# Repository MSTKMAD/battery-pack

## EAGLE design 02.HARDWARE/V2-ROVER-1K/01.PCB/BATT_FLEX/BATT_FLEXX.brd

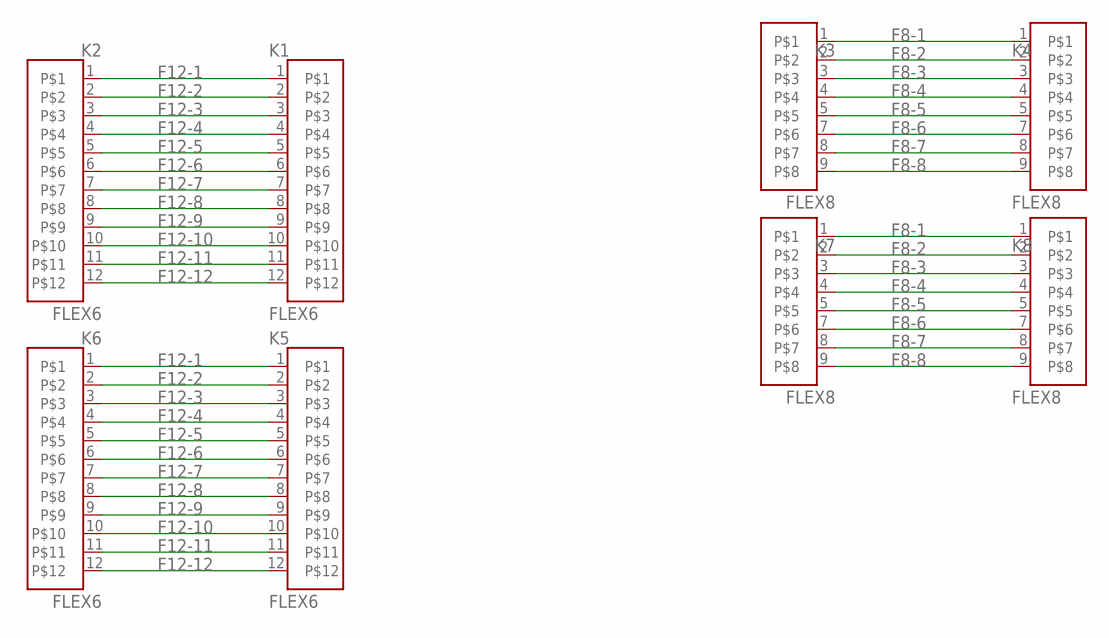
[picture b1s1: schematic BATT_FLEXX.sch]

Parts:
K1, K2, K5, K6: FLEX6
K3, K4, K7, K8: FLEX8

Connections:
F8-1: K3.1, K4.1, K7.1, K8.1
F8-2: K3.2, K4.2, K7.2, K8.2
F8-3: K3.3, K4.3, K7.3, K8.3
F8-4: K3.4, K4.4, K7.4, K8.4
F8-5: K3.5, K4.5, K7.5, K8.5
F8-6: K3.7, K4.7, K7.7, K8.7
F8-7: K3.8, K4.8, K7.8, K8.8
F8-8: K3.9, K4.9, K7.9, K8.9
F12-1: K1.1, K2.1, K5.1, K6.1
F12-2: K1.2, K2.2, K5.2, K6.2
F12-3: K1.3, K2.3, K5.3, K6.3
F12-4: K1.4, K2.4, K5.4, K6.4
F12-5: K1.5, K2.5, K5.5, K6.5
F12-6: K1.6, K2.6, K5.6, K6.6
F12-7: K1.7, K2.7, K5.7, K6.7
F12-8: K1.8, K2.8, K5.8, K6.8
F12-9: K1.9, K2.9, K5.9, K6.9
F12-10: K1.10, K2.10, K5.10, K6.10
F12-11: K1.11, K2.11, K5.11, K6.11
F12-12: K1.12, K2.12, K5.12, K6.12

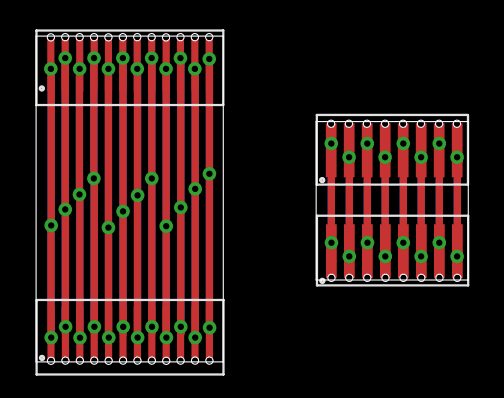
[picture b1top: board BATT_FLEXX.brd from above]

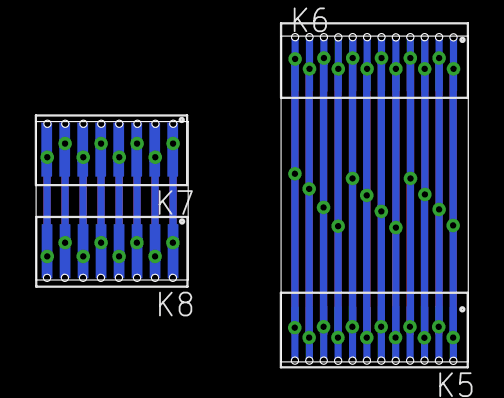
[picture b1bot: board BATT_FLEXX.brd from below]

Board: 2 copper layers, 24.0 x 18.1 mm, 8 parts (4 on the bottom side), 20 nets.

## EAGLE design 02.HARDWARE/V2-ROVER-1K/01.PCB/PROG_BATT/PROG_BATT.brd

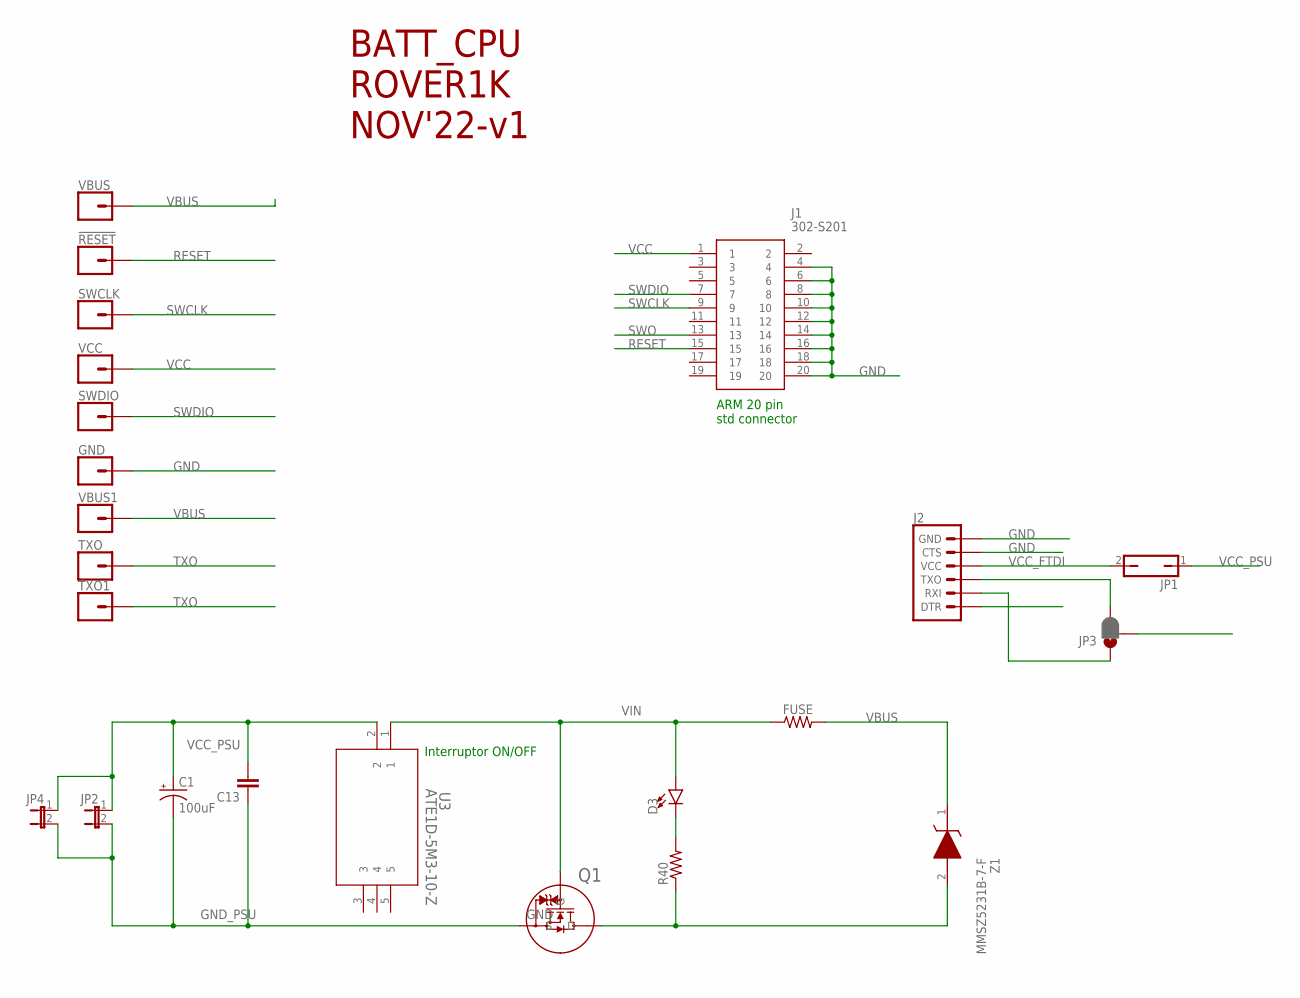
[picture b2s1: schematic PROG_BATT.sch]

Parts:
!RESET: CONN_01POGOPIN_HOLE_LARGE; 1X01_POGOPIN_HOLE_0.061_DIA
C1: 100uF; CPOL-RADIAL-2.5MM-6.5MM
C13: C-EUC0805; C0805
D3: LED3MM; LED_3MM
FUSE: 0805
GND: CONN_01POGOPIN_HOLE_LARGE; 1X01_POGOPIN_HOLE_0.061_DIA
J1: 302-S201; SHDR20W66P254_2X10_3300X905X90
J2: 6_PIN_SERIAL_TARGET; 1X06
JP1: JP1Q; JP1
JP2, JP4: JP1E; JP1
JP3: JUMPER-SMT_3_1-NC_PASTE_NO-SILK; SMT-JUMPER_3_1-NC_PASTE_NO-SILK
Q1: PJA3416AE_R1_00001; SOT23_PJA3416_PNJ
R40: 10K; 0805
SWCLK: CONN_01POGOPIN_HOLE_LARGE; 1X01_POGOPIN_HOLE_0.061_DIA
SWDIO: CONN_01POGOPIN_HOLE_LARGE; 1X01_POGOPIN_HOLE_0.061_DIA
TXO, TXO1: CONN_01POGOPIN_HOLE_LARGE; 1X01_POGOPIN_HOLE_0.061_DIA
U3: ATE1D-5M3-10-Z; SPDT05_ATE1D_9P5X8_NDC
VBUS, VBUS1: CONN_01POGOPIN_HOLE_LARGE; 1X01_POGOPIN_HOLE_0.061_DIA
VCC: CONN_01POGOPIN_HOLE_LARGE; 1X01_POGOPIN_HOLE_0.061_DIA
Z1: MMSZ5231B-7-F; SOD3716X145N

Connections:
GND: GND.2, J1.4, J1.6, J1.8, J1.10, J1.12, J1.14, J1.16, J1.18, J1.20, J2.5 (CTS), J2.6 (GND), Q1.3 (D), R40.1, Z1.2 (A)
GND_PSU: C1.2 (-), C13.1, JP2.2, JP4.2, Q1.2 (S)
unnamed: J2.2 (RXI), JP3.1
unnamed: J2.3 (TXO), JP3.3
unnamed: D3.K (C), R40.2
RESET: !RESET.2, J1.15
SWCLK: J1.9, SWCLK.2
SWDIO: J1.7, SWDIO.2
SWO: J1.13
TXO: JP3.2, TXO.2, TXO1.2
VBUS: FUSE.2, VBUS.2, VBUS1.2, Z1.1 (K)
VCC: J1.1, VCC.2
VCC_FTDI: J2.4 (VCC), JP1.2
VCC_PSU: C1.1 (+), C13.2, JP1.1, JP2.1, JP4.1, U3.2
VIN: D3.A, FUSE.1, Q1.1 (G), U3.1

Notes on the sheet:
BATT_CPU ROVER1K NOV'22-v1
ARM 20 pin std connector
Interruptor ON/OFF

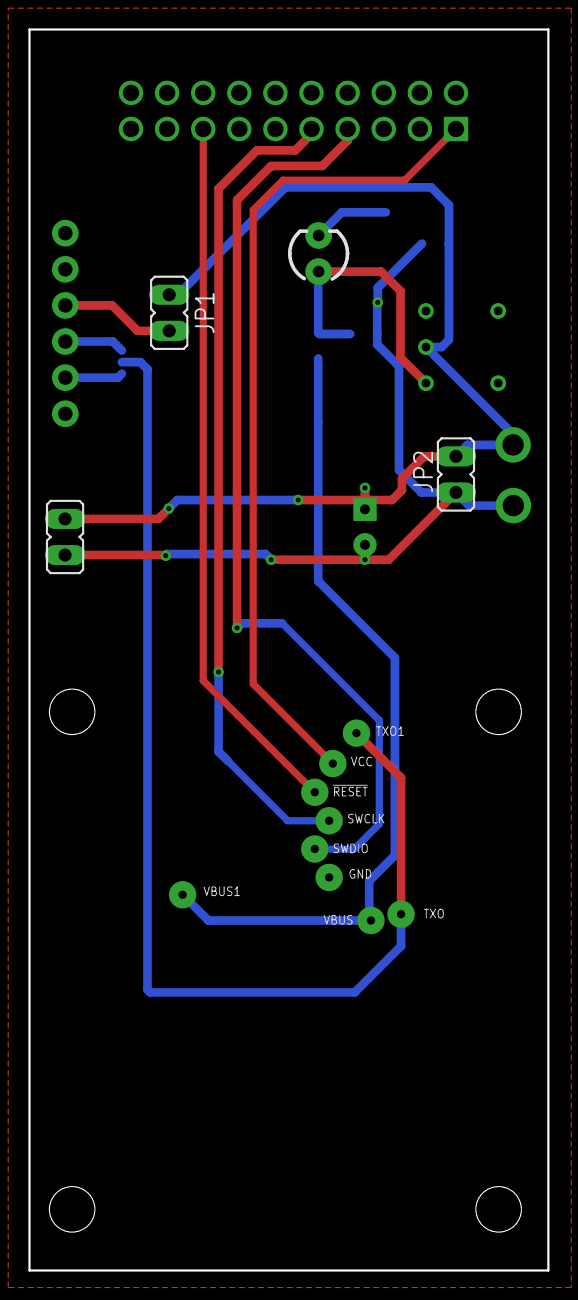
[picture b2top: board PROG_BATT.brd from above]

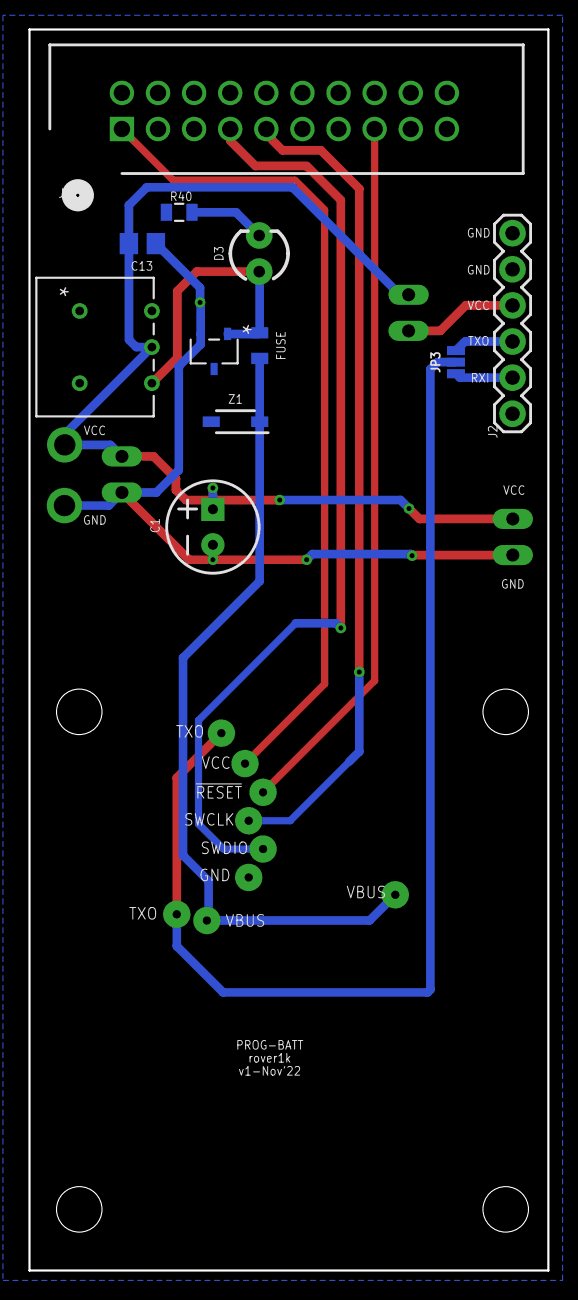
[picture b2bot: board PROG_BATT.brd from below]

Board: 2 copper layers, 36.5 x 87.3 mm, 23 parts (11 on the bottom side), 14 nets.

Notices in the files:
parts and their libraries:
SparkFun-Connectors: Licensing: Creative Commons ShareAlike 4.0 International - https://creativecommons.org/licenses/by-sa/4.0
COPYRIGHT: Copyright (C) 2022 Ultra Librarian. All rights reserved.
